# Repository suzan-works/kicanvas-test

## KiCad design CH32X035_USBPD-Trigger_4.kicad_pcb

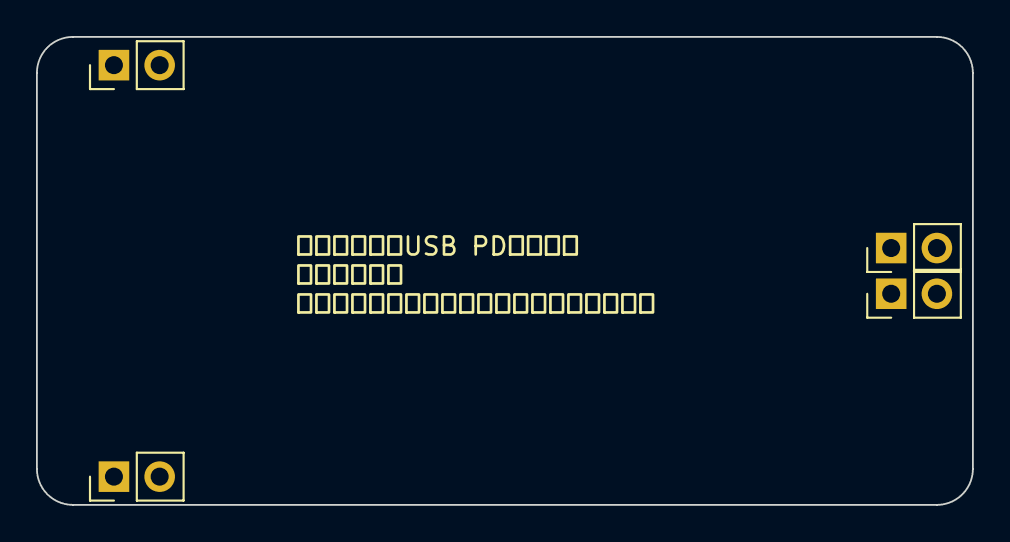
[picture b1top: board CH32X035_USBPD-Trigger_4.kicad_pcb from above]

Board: 2 copper layers, 52.0 x 26.0 mm, 4 parts (0 on the bottom side), 2 nets, no tracks yet.

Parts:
J3, J4, J6, J7: Conn_01x02; PinHeader_1x02_P2.54mm_Vertical

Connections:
GND: J4.1, J4.2
unnamed: J3.1, J3.2

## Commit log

2024-01-08 upload test
